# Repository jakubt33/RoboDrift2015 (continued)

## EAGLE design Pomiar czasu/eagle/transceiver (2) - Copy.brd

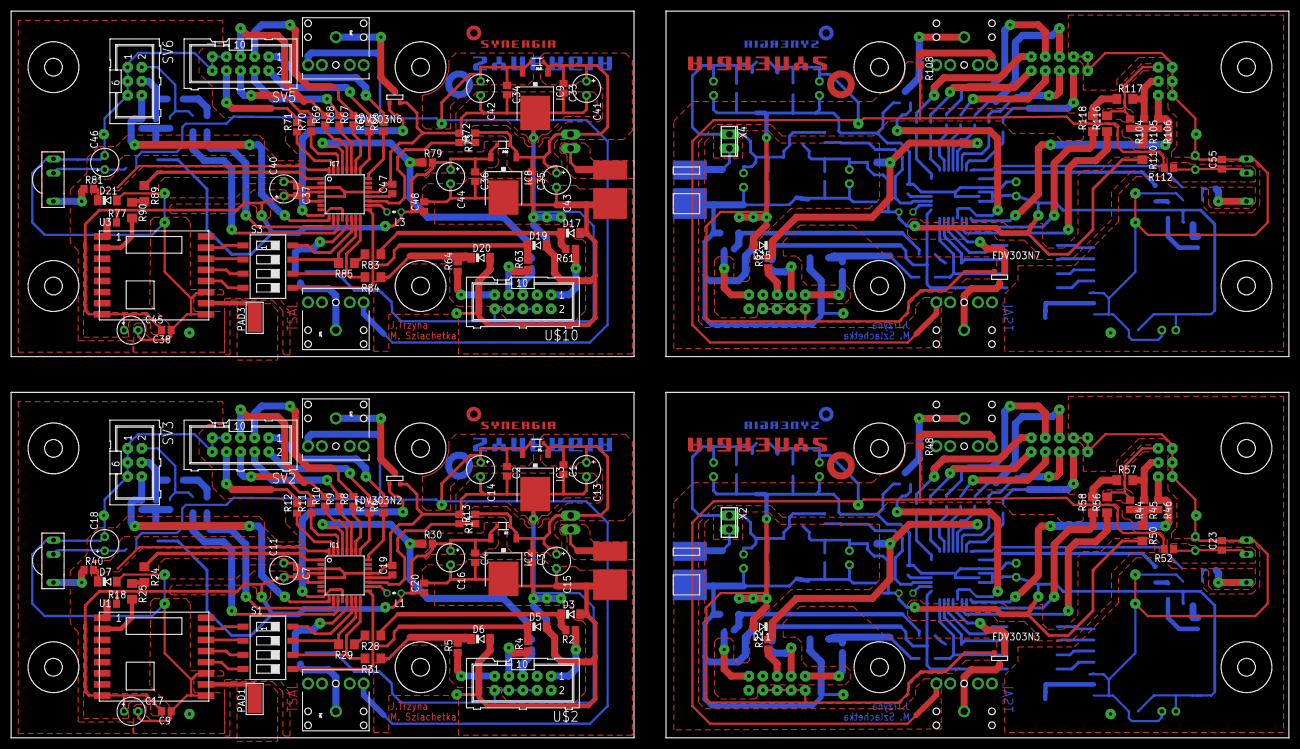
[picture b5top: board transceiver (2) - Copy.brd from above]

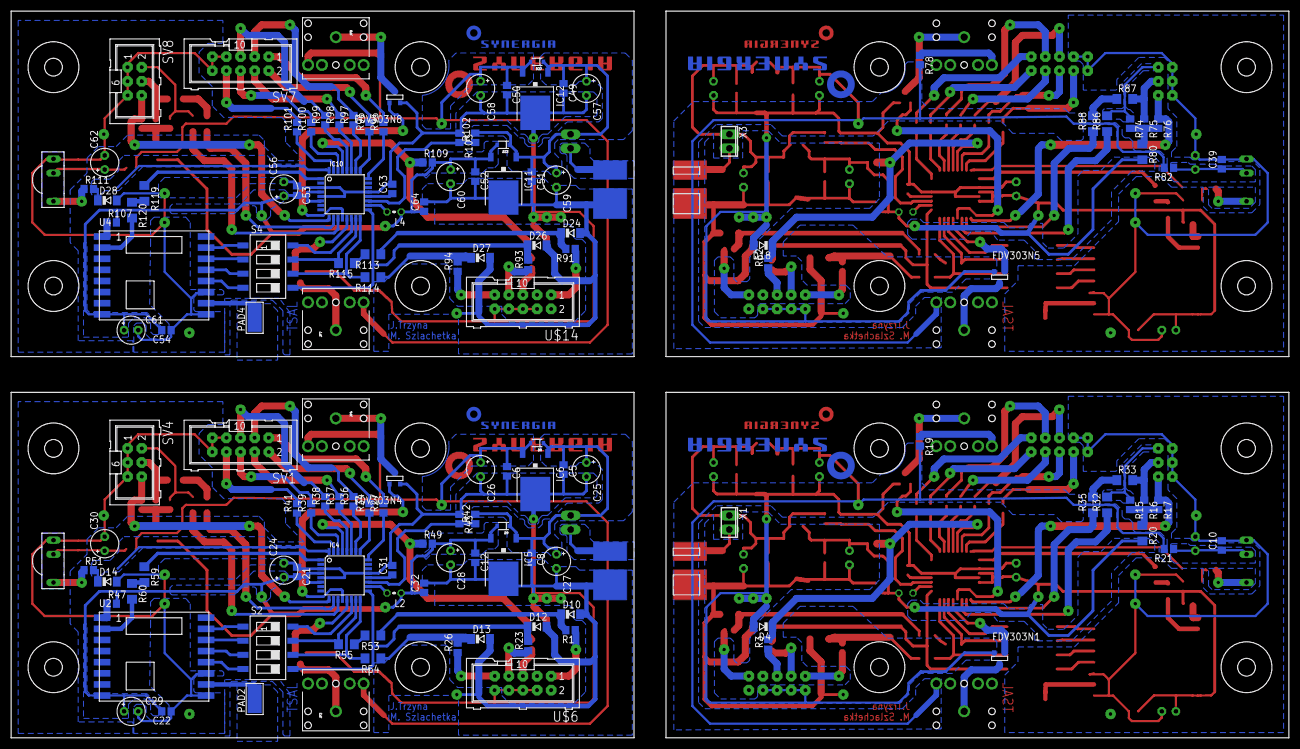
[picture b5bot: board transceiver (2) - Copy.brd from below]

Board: 2 copper layers, 229.9 x 130.7 mm, 288 parts (144 on the bottom side), 232 nets.

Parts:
C1, C2, C3, C4, C5, C6, C7, C8, C9, C10, C12, C19, C20, C21, C22, C23, C31, C32, C33, C34, C35, C36, C37, C38, C39, C47, C48, C49, C50, C51, C52, C53, C54, C55, C63, C64: 100n; C0805
C11, C17, C24, C29, C40, C45, C56, C61: 22u; E2,5-5
C13, C14, C15, C16, C25, C26, C27, C28, C41, C42, C43, C44, C57, C58, C59, C60: 47u; E2,5-5
C18, C30, C46, C62: 4,7u; E2,5-5
D1, D2, D8, D9, D15, D16, D22, D23: BAS16HT1G; SOD-323
D3, D4, D5, D6, D7, D10, D11, D12, D13, D14, D17, D18, D19, D20, D21, D24, D25, D26, D27, D28: SOD80C
FDV303N1, FDV303N2, FDV303N3, FDV303N4, FDV303N5, FDV303N6, FDV303N7, FDV303N8: SOT-23
IC1, IC4, IC7, IC10: MEGA8-AI; TQFP32-08
IC2, IC5, IC8, IC11: LF33; TO252
IC3, IC6, IC9, IC12: LF50; TO252
JP1, JP2, JP3, JP4, JP5, JP6, JP7, JP8: AUDIO-JACK
L1, L2, L3, L4: 0204V
PAD1, PAD2, PAD3, PAD4: WIREPADSMD5-2,5; 5-2,5
R1, R2, R3, R4, R5, R22, R23, R26, R61, R62, R63, R64, R91, R92, R93, R94: 330k; R0805
R6, R7, R8, R9, R10, R12, R27, R34, R36, R37, R38, R41, R65, R66, R67, R68, R69, R71, R95, R96, R97, R98, R99, R101: 1.2k; R0805
R11, R39, R70, R100: 1,2k; R0805
R13, R15, R16, R17, R18, R30, R42, R44, R45, R46, R47, R49, R72, R74, R75, R76, R77, R79, R102, R104, R105, R106, R107, R109: 10k; R0805
R14, R43, R73, R103: 3,6k; R0805
R19, R48, R78, R108: R0805
R20, R24, R25, R28, R29, R31, R32, R33, R35, R50, R53, R54, R55, R56, R57, R58, R59, R60, R80, R83, R84, R85, R86, R87, R88, R89, R90, R110, R113, R114, R115, R116, R117, R118, R119, R120: 0R; R1206
R21, R40, R51, R52, R81, R82, R111, R112: 220R; R0805
S1, S2, S3, S4: SWS004; SMS-004
SV1, SV2, SV5, SV7: ML10
SV3, SV4, SV6, SV8: ML6
TSOP, TSOP1, TSOP2, TSOP3: TSOP1736; TSOP17XX
U1, U2, U3, U4: RFM69HW; RFM69W-XXXS2
U$1, U$5, U$9, U$13: DEANS.MALE; DEANSM
U$2, U$6, U$10, U$14: ML10
U$3, U$7, U$11, U$15: SYNERGIA_16MM
U$4, U$8, U$12, U$16: SYNERGIA_30MM
X1, X2, X3, X4: 2POL254

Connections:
+3V1: C12.1, C21.2, C22.2, C24.+, C28.+, C29.+, C32.1, D9.2, IC4.4, IC4.6, IC5.2, L2.1, R47.2, R49.2, R50.2, U2.8
+3V2: C36.1, C37.2, C38.2, C40.+, C44.+, C45.+, C48.1, D16.2, IC7.4, IC7.6, IC8.2, L3.1, R77.2, R79.2, R80.2, U3.8
+3V3: C4.1, C7.2, C9.2, C11.+, C16.+, C17.+, C20.1, D2.2, IC1.4, IC1.6, IC2.2, L1.1, R18.2, R20.2, R30.2, U1.8
+3V4: C52.1, C53.2, C54.2, C56.+, C60.+, C61.+, C64.1, D23.2, IC10.4, IC10.6, IC11.2, L4.1, R107.2, R109.2, R110.2, U4.8
+5V: C2.1, C14.+, D1.2, IC3.2, JP1.TIP, R19.2, R21.2
+5V1: C6.1, C26.+, D8.2, IC6.2, JP2.TIP, R48.2, R52.2
+5V2: C34.1, C42.+, D15.2, IC9.2, JP5.TIP, R78.2, R82.2
+5V3: C50.1, C58.+, D22.2, IC12.2, JP7.TIP, R108.2, R112.2
ADC: IC1.19, R13.1, R14.2
ADC1: IC4.19, R42.1, R43.2
ADC2: IC7.19, R72.1, R73.2
ADC3: IC10.19, R102.1, R103.2
DIO0: IC1.1, R24.1
DIO1: IC4.1, R59.1
DIO2: IC7.1, R89.1
DIO3: IC10.1, R119.1
GND: C1.2, C2.2, C3.2, C4.2, C7.1, C9.1, C10.2, C11.-, C13.-, C14.-, C15.-, C16.-, C17.-, C18.-, C19.2, C20.2, D3.A, D4.A, D5.A, D6.A, D7.A, FDV303N1.2, FDV303N2.2, IC1.3, IC1.5, IC1.21, IC2.3, IC3.3, R14.1, SV2.7, SV2.9, SV2.10, SV3.1, SV3.3, SV3.5, TSOP.GND, U1.9, U1.11, U$1.P$NEG, U$2.4, U$2.6, U$2.8, U$2.10
GND1: C5.2, C6.2, C8.2, C12.2, C21.1, C22.1, C23.2, C24.-, C25.-, C26.-, C27.-, C28.-, C29.-, C30.-, C31.2, C32.2, D10.A, D11.A, D12.A, D13.A, D14.A, FDV303N3.2, FDV303N4.2, IC4.3, IC4.5, IC4.21, IC5.3, IC6.3, R43.1, SV1.7, SV1.9, SV1.10, SV4.1, SV4.3, SV4.5, TSOP1.GND, U2.9, U2.11, U$5.P$NEG, U$6.4, U$6.6, U$6.8, U$6.10
GND2: C33.2, C34.2, C35.2, C36.2, C37.1, C38.1, C39.2, C40.-, C41.-, C42.-, C43.-, C44.-, C45.-, C46.-, C47.2, C48.2, D17.A, D18.A, D19.A, D20.A, D21.A, FDV303N5.2, FDV303N6.2, IC7.3, IC7.5, IC7.21, IC8.3, IC9.3, R73.1, SV5.7, SV5.9, SV5.10, SV6.1, SV6.3, SV6.5, TSOP2.GND, U3.9, U3.11, U$9.P$NEG, U$10.4, U$10.6, U$10.8, U$10.10
GND3: C49.2, C50.2, C51.2, C52.2, C53.1, C54.1, C55.2, C56.-, C57.-, C58.-, C59.-, C60.-, C61.-, C62.-, C63.2, C64.2, D24.A, D25.A, D26.A, D27.A, D28.A, FDV303N7.2, FDV303N8.2, IC10.3, IC10.5, IC10.21, IC11.3, IC12.3, R103.1, SV7.7, SV7.9, SV7.10, SV8.1, SV8.3, SV8.5, TSOP3.GND, U4.9, U4.11, U$13.P$NEG, U$14.4, U$14.6, U$14.8, U$14.10
LED1: IC1.24, R6.1
LED2: IC1.25, R7.1
LED3: IC1.26, R8.1
LED4: IC1.27, R9.1
LED5: IC1.28, R10.1
LED6: IC4.24, R27.1
LED7: IC4.25, R34.1
LED8: IC4.26, R36.1
LED9: IC4.27, R37.1
LED10: IC4.28, R38.1
LED11: IC7.24, R65.1
LED12: IC7.25, R66.1
LED13: IC7.26, R67.1
LED14: IC7.27, R68.1
LED15: IC7.28, R69.1
LED16: IC10.24, R95.1
LED17: IC10.25, R96.1
LED18: IC10.26, R97.1
LED19: IC10.27, R98.1
LED20: IC10.28, R99.1
LED_BATT_GR: IC1.30, R11.1
LED_BATT_GR1: IC4.30, R39.1
LED_BATT_GR2: IC7.30, R70.1
LED_BATT_GR3: IC10.30, R100.1
LED_BATT_RED: IC1.31, R12.1
LED_BATT_RED1: IC4.31, R41.1
LED_BATT_RED2: IC7.31, R71.1
LED_BATT_RED3: IC10.31, R101.1
LED_STRIPE: FDV303N2.3, IC1.12
LED_STRIPE1: FDV303N4.3, IC4.12
LED_STRIPE2: FDV303N6.3, IC7.12
LED_STRIPE3: FDV303N8.3, IC10.12
MISO: IC1.16, R31.2, S1.6
MISO1: IC4.16, R54.2, S2.6
MISO2: IC7.16, R84.2, S3.6
MISO3: IC10.16, R114.2, S4.6
MOSI: IC1.15, R29.2, S1.7
MOSI1: IC4.15, R55.2, S2.7
MOSI2: IC7.15, R85.2, S3.7
MOSI3: IC10.15, R115.2, S4.7
unnamed: R40.1, TSOP.OUT
unnamed: IC1.18, L1.2
unnamed: R1.1, U$6.1
unnamed: R2.1, U$2.1
unnamed: R3.1, U$2.5
unnamed: R4.1, U$2.7
unnamed: R5.1, U$2.9
unnamed: R22.1, U$6.5
unnamed: R6.2, SV2.1
unnamed: R7.2, SV2.2
unnamed: R8.2, SV2.3
unnamed: R9.2, SV2.4
unnamed: R10.2, SV2.5
unnamed: FDV303N1.1, JP1.SLEEVE
unnamed: FDV303N2.1, JP3.SLEEVE
unnamed: R11.2, SV2.6
unnamed: R12.2, SV2.8
unnamed: U$1.P$POS, X1.2
unnamed: JP3.TIP, R19.1
unnamed: R18.1, U1.1
unnamed: R23.1, U$6.7
unnamed: R15.2, R16.2, R17.2, R20.1
unnamed: R24.2, R25.1
unnamed: C10.1, C18.+, R21.1, TSOP.V+
unnamed: C19.1, IC1.20
unnamed: C1.1, C3.1, C13.+, C15.+, D1.1, D2.1, IC2.1, IC3.1, R13.2, X1.1
unnamed: PAD1.1, U1.10
unnamed: R28.2, R29.1
unnamed: D3.C, R2.2, R28.1
unnamed: D6.C, R5.2, R31.1
unnamed: R15.1, R32.2, SV3.2
unnamed: R16.1, R33.2, SV3.4
unnamed: R33.1, R35.2
unnamed: S1.3, U1.13
unnamed: S1.2, U1.14
unnamed: S1.4, U1.12
unnamed: S1.1, U1.15
unnamed: R26.1, U$6.9
unnamed: R47.1, U2.1
unnamed: C5.1, C8.1, C25.+, C27.+, D8.1, D9.1, IC5.1, IC6.1, R42.2, X2.1
unnamed: IC4.18, L2.2
unnamed: C31.1, IC4.20
unnamed: R25.2, U1.2
unnamed: PAD2.1, U2.10
unnamed: R27.2, SV1.1
unnamed: R34.2, SV1.2
unnamed: R36.2, SV1.3
unnamed: R37.2, SV1.4
unnamed: R38.2, SV1.5
unnamed: R39.2, SV1.6
unnamed: R41.2, SV1.8
unnamed: U$5.P$POS, X2.2
unnamed: FDV303N3.1, JP2.SLEEVE
unnamed: FDV303N4.1, JP4.SLEEVE
unnamed: JP4.TIP, R48.1
unnamed: R51.1, TSOP1.OUT
unnamed: C23.1, C30.+, R52.1, TSOP1.V+
unnamed: R44.2, R45.2, R46.2, R50.1
unnamed: D10.C, R1.2, R53.1
unnamed: D13.C, R26.2, R54.1
unnamed: R53.2, R55.1
unnamed: R44.1, R56.2, SV4.2
unnamed: R45.1, R57.2, SV4.4
unnamed: R57.1, R58.2
unnamed: S2.1, U2.15
unnamed: S2.2, U2.14
unnamed: S2.3, U2.13
unnamed: S2.4, U2.12
unnamed: R59.2, R60.1
unnamed: R60.2, U2.2
unnamed: R61.1, U$10.1
unnamed: R62.1, U$10.5
unnamed: R63.1, U$10.7
unnamed: R64.1, U$10.9
unnamed: R77.1, U3.1
unnamed: C33.1, C35.1, C41.+, C43.+, D15.1, D16.1, IC8.1, IC9.1, R72.2, X3.1
unnamed: IC7.18, L3.2
unnamed: C47.1, IC7.20
unnamed: PAD3.1, U3.10
unnamed: R65.2, SV5.1
unnamed: R66.2, SV5.2
unnamed: R67.2, SV5.3
unnamed: R68.2, SV5.4
unnamed: R69.2, SV5.5
unnamed: R70.2, SV5.6
unnamed: R71.2, SV5.8
unnamed: U$9.P$POS, X3.2
unnamed: FDV303N5.1, JP5.SLEEVE
unnamed: FDV303N6.1, JP6.SLEEVE
unnamed: JP6.TIP, R78.1
unnamed: R81.1, TSOP2.OUT
unnamed: C39.1, C46.+, R82.1, TSOP2.V+
unnamed: R74.2, R75.2, R76.2, R80.1
unnamed: D17.C, R61.2, R83.1
unnamed: D20.C, R64.2, R84.1
unnamed: R83.2, R85.1
unnamed: R74.1, R86.2, SV6.2
unnamed: R75.1, R87.2, SV6.4
unnamed: R87.1, R88.2
unnamed: S3.1, U3.15
unnamed: S3.2, U3.14
unnamed: S3.3, U3.13
unnamed: S3.4, U3.12
unnamed: R89.2, R90.1
unnamed: R90.2, U3.2
unnamed: R91.1, U$14.1
unnamed: R92.1, U$14.5
unnamed: R93.1, U$14.7
unnamed: R94.1, U$14.9
unnamed: R107.1, U4.1
unnamed: C49.1, C51.1, C57.+, C59.+, D22.1, D23.1, IC11.1, IC12.1, R102.2, X4.1
unnamed: IC10.18, L4.2
unnamed: C63.1, IC10.20
unnamed: PAD4.1, U4.10
unnamed: R95.2, SV7.1
unnamed: R96.2, SV7.2
unnamed: R97.2, SV7.3
unnamed: R98.2, SV7.4
unnamed: R99.2, SV7.5
unnamed: R100.2, SV7.6
unnamed: R101.2, SV7.8
unnamed: U$13.P$POS, X4.2
unnamed: FDV303N7.1, JP7.SLEEVE
unnamed: FDV303N8.1, JP8.SLEEVE
unnamed: JP8.TIP, R108.1
unnamed: R111.1, TSOP3.OUT
unnamed: C55.1, C62.+, R112.1, TSOP3.V+
unnamed: R104.2, R105.2, R106.2, R110.1
unnamed: D24.C, R91.2, R113.1
unnamed: D27.C, R94.2, R114.1
unnamed: R113.2, R115.1
unnamed: R104.1, R116.2, SV8.2
unnamed: R105.1, R117.2, SV8.4
unnamed: R117.1, R118.2
unnamed: S4.1, U4.15
unnamed: S4.2, U4.14
unnamed: S4.3, U4.13
unnamed: S4.4, U4.12
unnamed: R119.2, R120.1
unnamed: R120.2, U4.2
RESET: D4.C, IC1.29, R3.2, R30.1
RESET1: D11.C, IC4.29, R22.2, R49.1
RESET2: D18.C, IC7.29, R62.2, R79.1
RESET3: D25.C, IC10.29, R92.2, R109.1
SCK: D5.C, IC1.17, R4.2, S1.5
SCK1: D12.C, IC4.17, R23.2, S2.5
SCK2: D19.C, IC7.17, R63.2, S3.5
SCK3: D26.C, IC10.17, R93.2, S4.5
SS: IC1.14, S1.8
SS1: IC4.14, S2.8
SS2: IC7.14, S3.8
SS3: IC10.14, S4.8
SWITCH_DOWN: IC1.11, R32.1
SWITCH_DOWN1: IC4.11, R56.1
SWITCH_DOWN2: IC7.11, R86.1
SWITCH_DOWN3: IC10.11, R116.1
SWITCH_OK: IC1.10, R35.1
SWITCH_OK1: IC4.10, R58.1
SWITCH_OK2: IC7.10, R88.1
SWITCH_OK3: IC10.10, R118.1
SWITCH_UP: IC1.9, R17.1, SV3.6
SWITCH_UP1: IC4.9, R46.1, SV4.6
SWITCH_UP2: IC7.9, R76.1, SV6.6
SWITCH_UP3: IC10.9, R106.1, SV8.6
TSAL_ENABLE: FDV303N1.3, IC1.13
TSAL_ENABLE1: FDV303N3.3, IC4.13
TSAL_ENABLE2: FDV303N5.3, IC7.13
TSAL_ENABLE3: FDV303N7.3, IC10.13
TSOP_OUT: D7.C, IC1.32, R40.2
TSOP_OUT1: D14.C, IC4.32, R51.2
TSOP_OUT2: D21.C, IC7.32, R81.2
TSOP_OUT3: D28.C, IC10.32, R111.2

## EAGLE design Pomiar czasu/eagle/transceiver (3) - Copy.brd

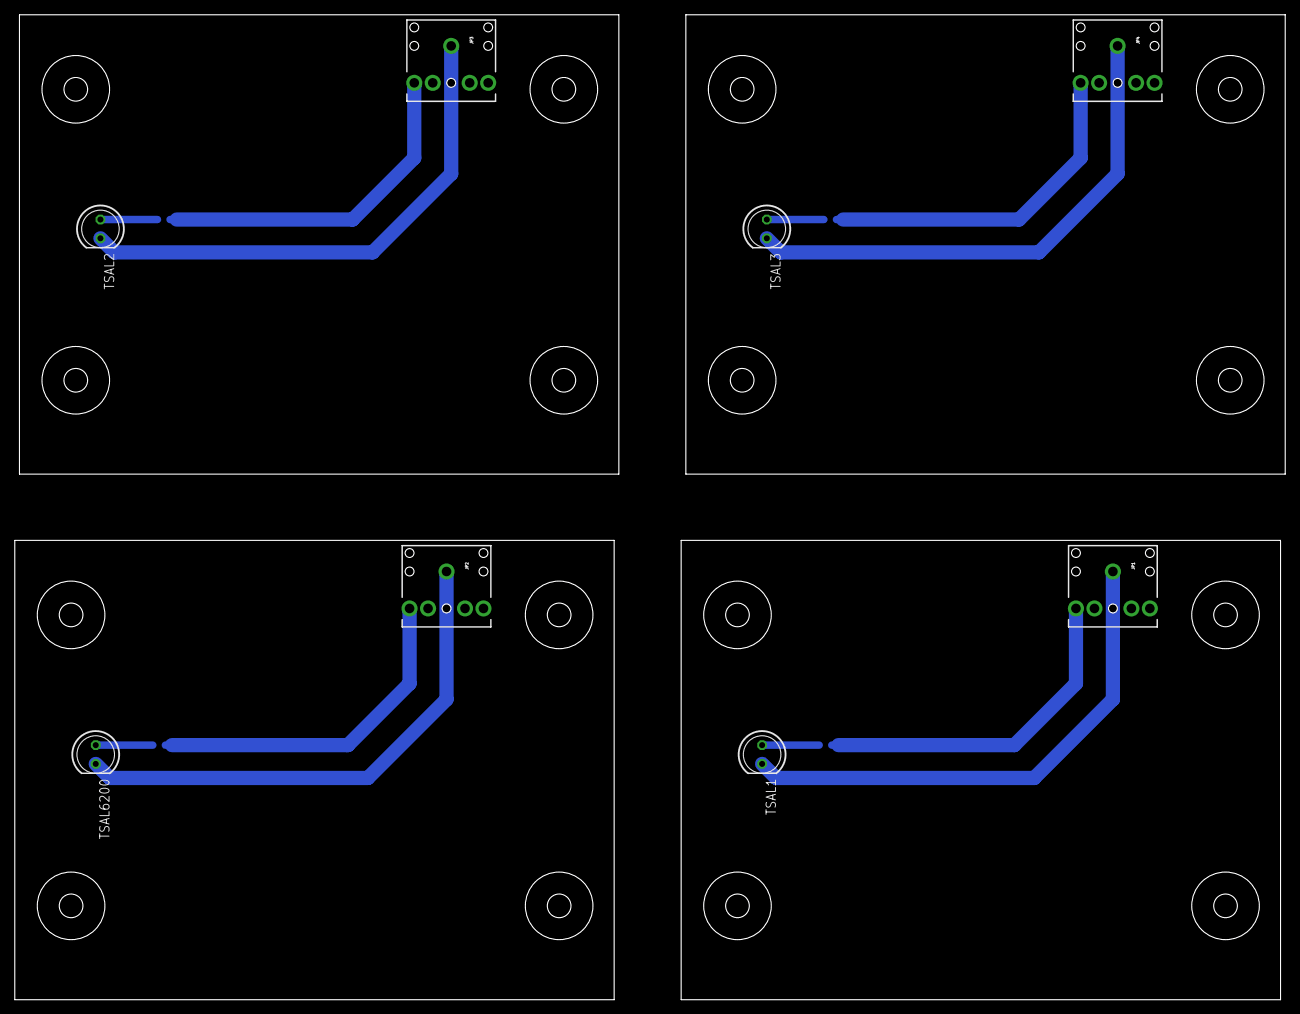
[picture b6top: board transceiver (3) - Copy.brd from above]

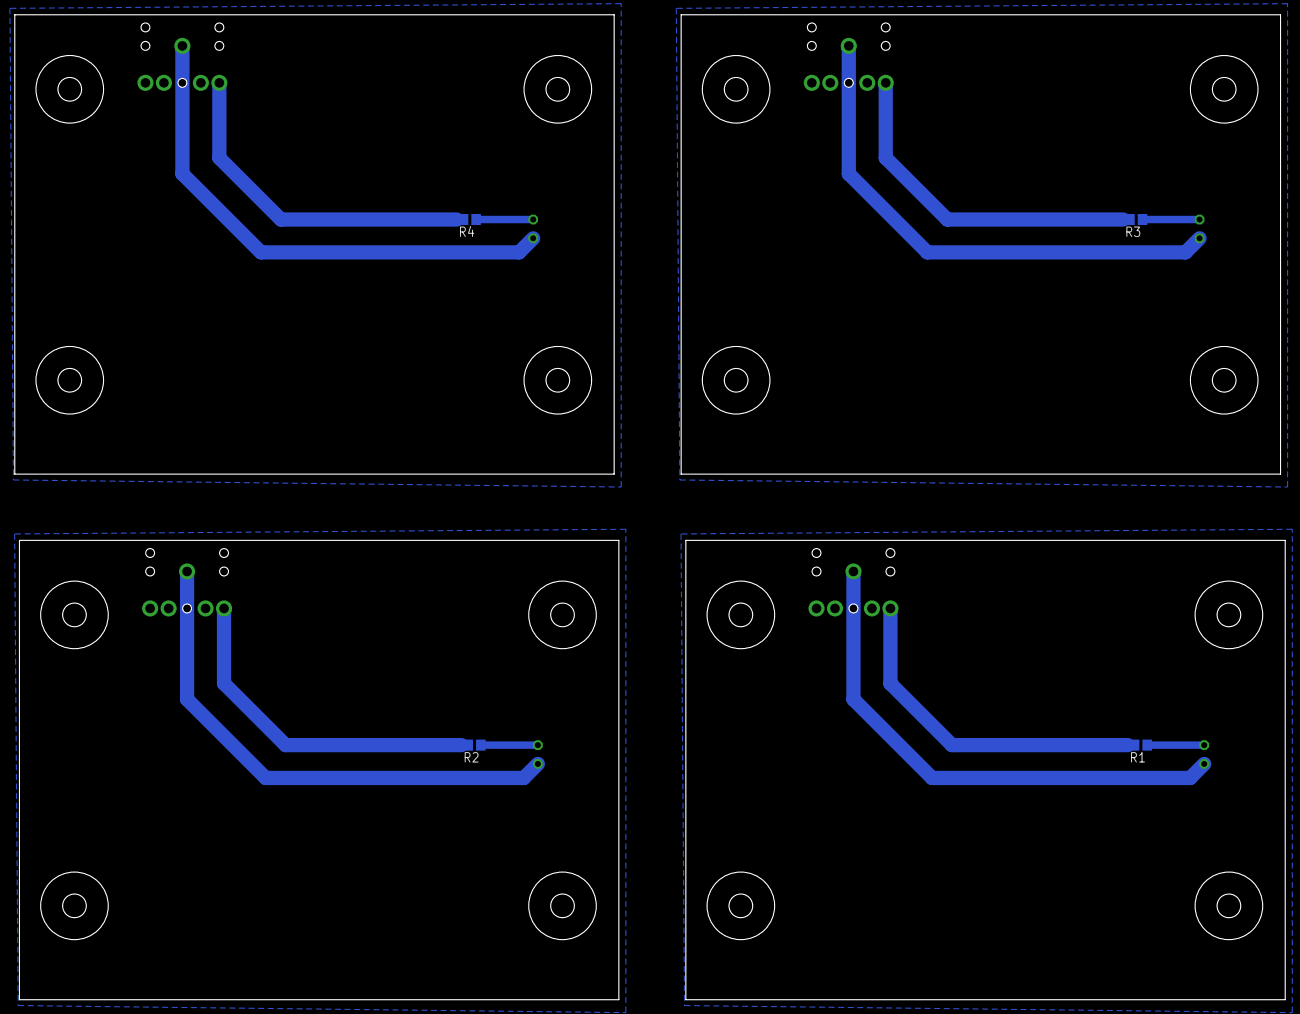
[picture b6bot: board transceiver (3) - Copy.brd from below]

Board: 2 copper layers, 171.9 x 133.3 mm, 12 parts (4 on the bottom side), 12 nets.

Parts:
JP1, JP2, JP3, JP4: AUDIO-JACK
R1, R2, R3, R4: 36,5R; R0805
TSAL1, TSAL2, TSAL3, TSAL6200: LED5MM

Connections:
unnamed: JP1.SLEEVE, TSAL1.K
unnamed: JP1.TIP, R2.2
unnamed: JP2.TIP, R1.2
unnamed: R2.1, TSAL1.A
unnamed: JP3.SLEEVE, TSAL2.K
unnamed: JP3.TIP, R3.2
unnamed: R3.1, TSAL2.A
unnamed: R1.1, TSAL6200.A
unnamed: JP4.SLEEVE, TSAL3.K
unnamed: JP4.TIP, R4.2
unnamed: R4.1, TSAL3.A
unnamed: JP2.SLEEVE, TSAL6200.K

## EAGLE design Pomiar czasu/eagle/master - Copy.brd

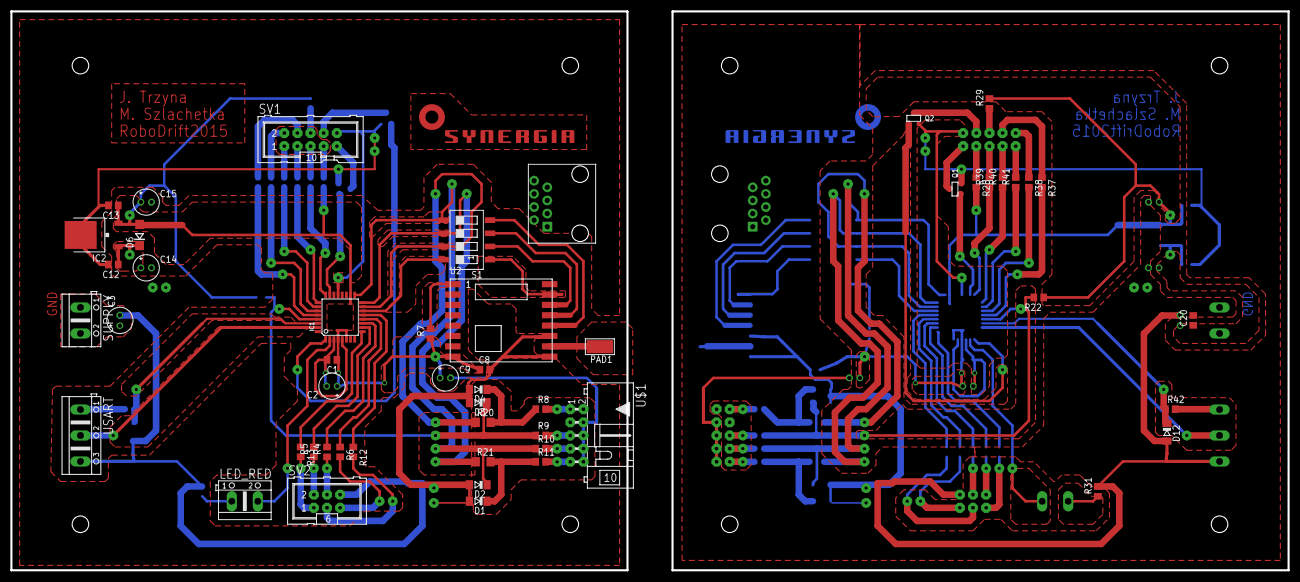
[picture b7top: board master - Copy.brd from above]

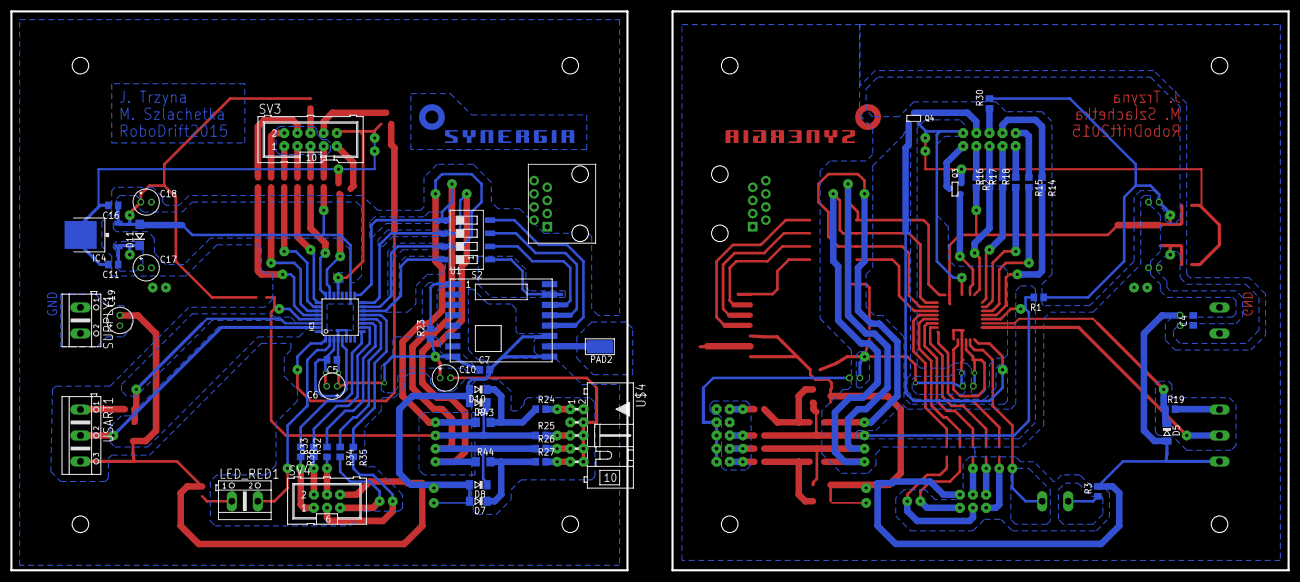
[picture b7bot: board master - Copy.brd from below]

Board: 2 copper layers, 246.7 x 107.9 mm, 106 parts (53 on the bottom side), 102 nets.

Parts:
C1, C4, C5, C7, C8, C11, C12, C13, C16, C20: 100n; C0805
C2, C6: 22uF; E2-5
C3, C19: 220uF; E2-5
C9, C10, C14, C15, C17, C18: 4.7uF; E2-5
D1, D2, D3, D4, D5, D7, D8, D9, D10, D12: 3.3V; SOD80C
D6, D11: BAS16HT1G; DO214AC
IC1, IC3: MEGA8-AI; TQFP32-08
IC2, IC4: lf33; TO252
LED_RED, LED_RED1: AK500/2
PAD1, PAD2: WIREPADSMD5-2,5; 5-2,5
Q1, Q2, Q3, Q4: SOT-23
R1, R7, R22, R23: 10k; R0805
R2, R3, R28, R29, R30, R31: 15R; R0805
R4, R5, R6, R12, R13, R14, R15, R16, R17, R18, R32, R33, R34, R35, R36, R37, R38, R39, R40, R41: 470; R0805
R8, R9, R10, R11, R19, R24, R25, R26, R27, R42: 220; R0805
R20, R21, R43, R44: 0R; R1206
S1, S2: SWS004; SMS-004
SUPPLY, SUPPLY1: AK500/2
SV1, SV3: ML10
SV2, SV4: ML6
U1, U2: RFM69HW; RFM69W-XXXS2
U$1, U$4: AVR_SPI_PROG2PTH2; ML10L
U$2, U$5: RJ45-8PTH; RJ45-8
U$3, U$6: SYNERGIA_30MM
USART, USART1: AK500/3

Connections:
+3V1: C5.1, C6.+, C7.1, C10.+, C16.1, C18.+, D11.A, IC3.4, IC3.6, IC3.18, IC4.2, R22.1, R23.1, R28.2, R29.2, U1.8
+3V3: C1.1, C2.+, C8.1, C9.+, C13.1, C15.+, D6.A, IC1.4, IC1.6, IC1.18, IC2.2, R1.1, R2.2, R7.1, R30.2, U2.8
GND: C1.2, C2.-, C3.-, C4.2, C8.2, C9.-, C12.2, C13.2, C14.-, C15.-, D1.A, D2.A, D3.A, D4.A, D5.A, IC1.3, IC1.5, IC1.21, IC2.3, Q3.2, Q4.2, R3.2, SUPPLY.1, SV1.10, SV2.6, U2.9, U2.11, U$1.4, U$1.6, U$1.8, U$1.10, USART.3
GND1: C5.2, C6.-, C7.2, C10.-, C11.2, C16.2, C17.-, C18.-, C19.-, C20.2, D7.A, D8.A, D9.A, D10.A, D12.A, IC3.3, IC3.5, IC3.21, IC4.3, Q1.2, Q2.2, R31.2, SUPPLY1.1, SV3.10, SV4.6, U1.9, U1.11, U$4.4, U$4.6, U$4.8, U$4.10, USART1.3
LED_FALSTART: R30.1, SV1.6
LED_FALSTART1: R29.1, SV3.6
LED_FALSTART_GATE: IC1.1, Q4.1
LED_FALSTART_GATE1: IC3.1, Q2.1
LED_FALSTART_GND: Q4.3, SV1.8
LED_FALSTART_GND1: Q2.3, SV3.8
LED_GO: R2.1, SV1.7
LED_GO1: R28.1, SV3.7
LED_GO_GATE: IC1.23, Q3.1
LED_GO_GATE1: IC3.23, Q1.1
LED_GO_GND: Q3.3, SV1.9
LED_GO_GND1: Q1.3, SV3.9
LED_RED: IC1.2, LED_RED.2
LED_RED1: IC3.2, LED_RED1.2
LED_S1: IC1.9, R13.1
LED_S2: IC1.10, R5.2
LED_S3: IC1.13, R12.1
LED_S4: IC1.11, R4.2
LED_S5: IC1.12, R6.1
LED_S6: IC3.9, R36.1
LED_S7: IC3.13, R35.1
LED_S8: IC3.12, R34.1
LED_S9: IC3.10, R33.2
LED_S10: IC3.11, R32.2
LED_Y1: IC1.26, R18.1
LED_Y2: IC1.27, R15.2
LED_Y3: IC1.25, R17.1
LED_Y4: IC1.28, R14.2
LED_Y5: IC1.24, R16.1
LED_Y6: IC3.26, R41.1
LED_Y7: IC3.27, R38.2
LED_Y8: IC3.25, R40.1
LED_Y9: IC3.28, R37.2
LED_Y10: IC3.24, R39.1
MISO: IC1.16, R21.1, S1.6
MISO1: IC3.16, R44.1, S2.6
MOSI: IC1.15, R20.1, S1.7
MOSI1: IC3.15, R43.1, S2.7
unnamed: D1.C, R11.1, R21.2
unnamed: D4.C, R8.1, R20.2
unnamed: LED_RED.1, R3.1
unnamed: R4.1, SV2.4
unnamed: R5.1, SV2.2
unnamed: R6.2, SV2.5
unnamed: R7.2, U2.1
unnamed: S1.1, U2.15
unnamed: PAD1.1, U2.10
unnamed: S1.4, U2.12
unnamed: S1.3, U2.13
unnamed: S1.2, U2.14
unnamed: R8.2, U$1.1
unnamed: R11.2, U$1.9
unnamed: R10.2, U$1.7
unnamed: R9.2, U$1.5
unnamed: R12.2, SV2.3
unnamed: R13.2, SV2.1
unnamed: R14.1, SV1.4
unnamed: R15.1, SV1.2
unnamed: R16.2, SV1.5
unnamed: R17.2, SV1.3
unnamed: R18.2, SV1.1
unnamed: R19.2, USART.1
unnamed: R23.2, U1.1
unnamed: PAD2.1, U1.10
unnamed: R24.2, U$4.1
unnamed: R27.2, U$4.9
unnamed: R26.2, U$4.7
unnamed: R25.2, U$4.5
unnamed: LED_RED1.1, R31.1
unnamed: R32.1, SV4.4
unnamed: R33.1, SV4.2
unnamed: R34.2, SV4.5
unnamed: R35.2, SV4.3
unnamed: R36.2, SV4.1
unnamed: R37.1, SV3.4
unnamed: R38.1, SV3.2
unnamed: R39.2, SV3.5
unnamed: R40.2, SV3.3
unnamed: R41.2, SV3.1
unnamed: R42.2, USART1.1
unnamed: D10.C, R24.1, R43.2
unnamed: D7.C, R27.1, R44.2
unnamed: S2.1, U1.15
unnamed: S2.4, U1.12
unnamed: S2.3, U1.13
unnamed: S2.2, U1.14
RESET: D3.C, IC1.29, R1.2, R9.1
RESET1: D9.C, IC3.29, R22.2, R25.1
RX: D5.C, IC1.30, R19.1
RX1: D12.C, IC3.30, R42.1
SCK: D2.C, IC1.17, R10.1, S1.5
SCK1: D8.C, IC3.17, R26.1, S2.5
SS: IC1.14, S1.8
SS1: IC3.14, S2.8
TXD: IC1.31, USART.2
TXD1: IC3.31, USART1.2
VCC: C3.+, C4.1, C12.1, C14.+, D6.C, IC2.1, SUPPLY.2
VCC1: C11.1, C17.+, C19.+, C20.1, D11.C, IC4.1, SUPPLY1.2

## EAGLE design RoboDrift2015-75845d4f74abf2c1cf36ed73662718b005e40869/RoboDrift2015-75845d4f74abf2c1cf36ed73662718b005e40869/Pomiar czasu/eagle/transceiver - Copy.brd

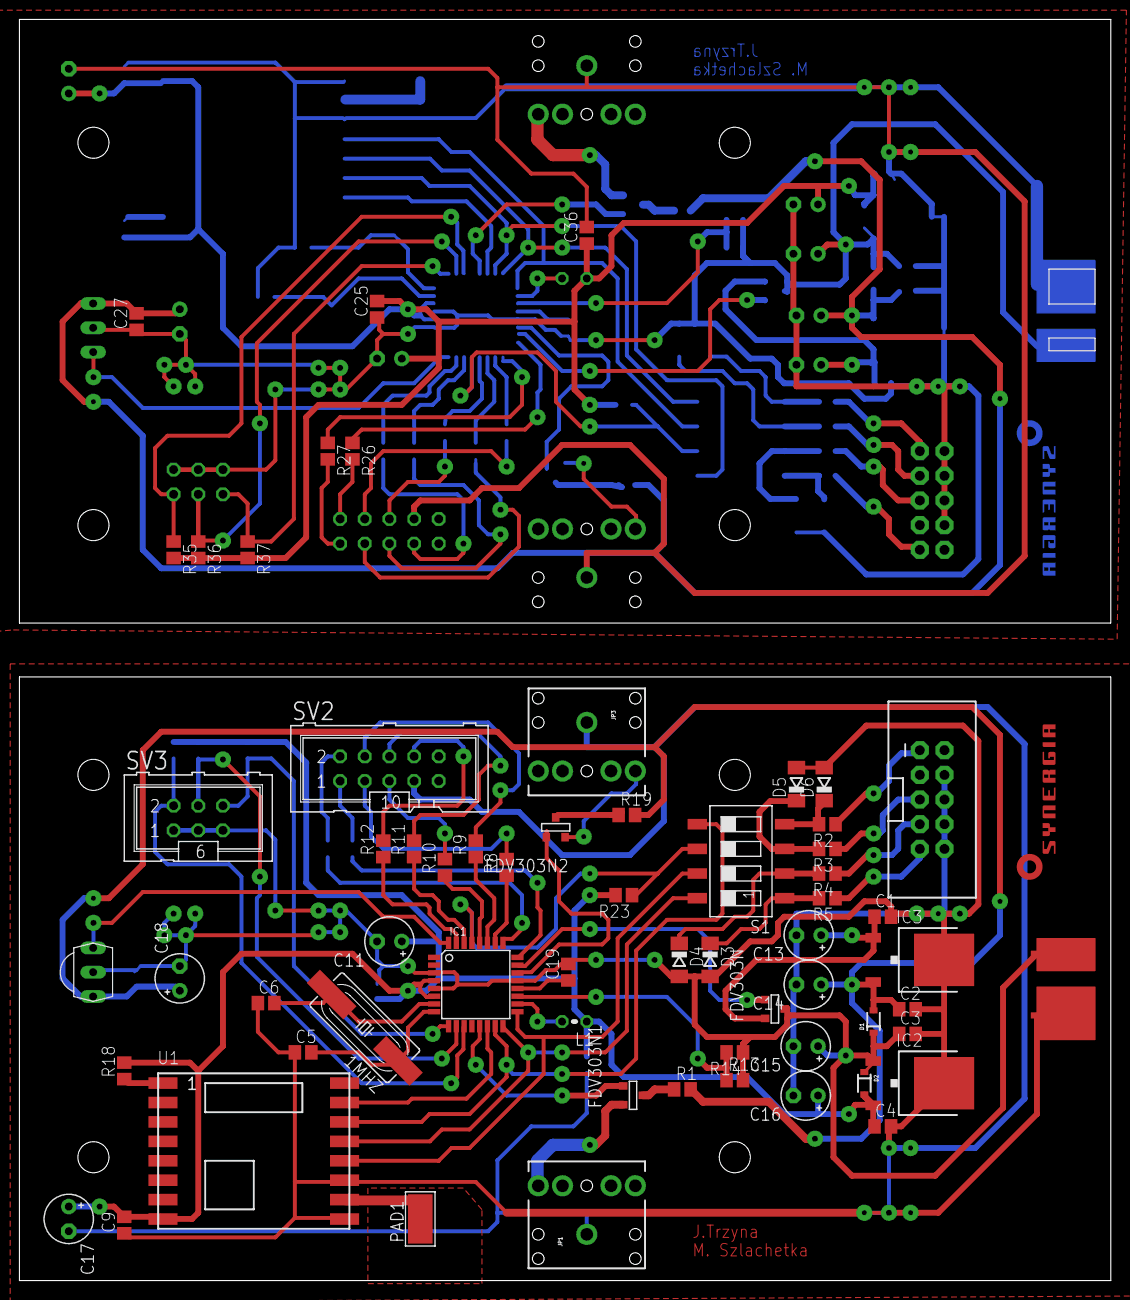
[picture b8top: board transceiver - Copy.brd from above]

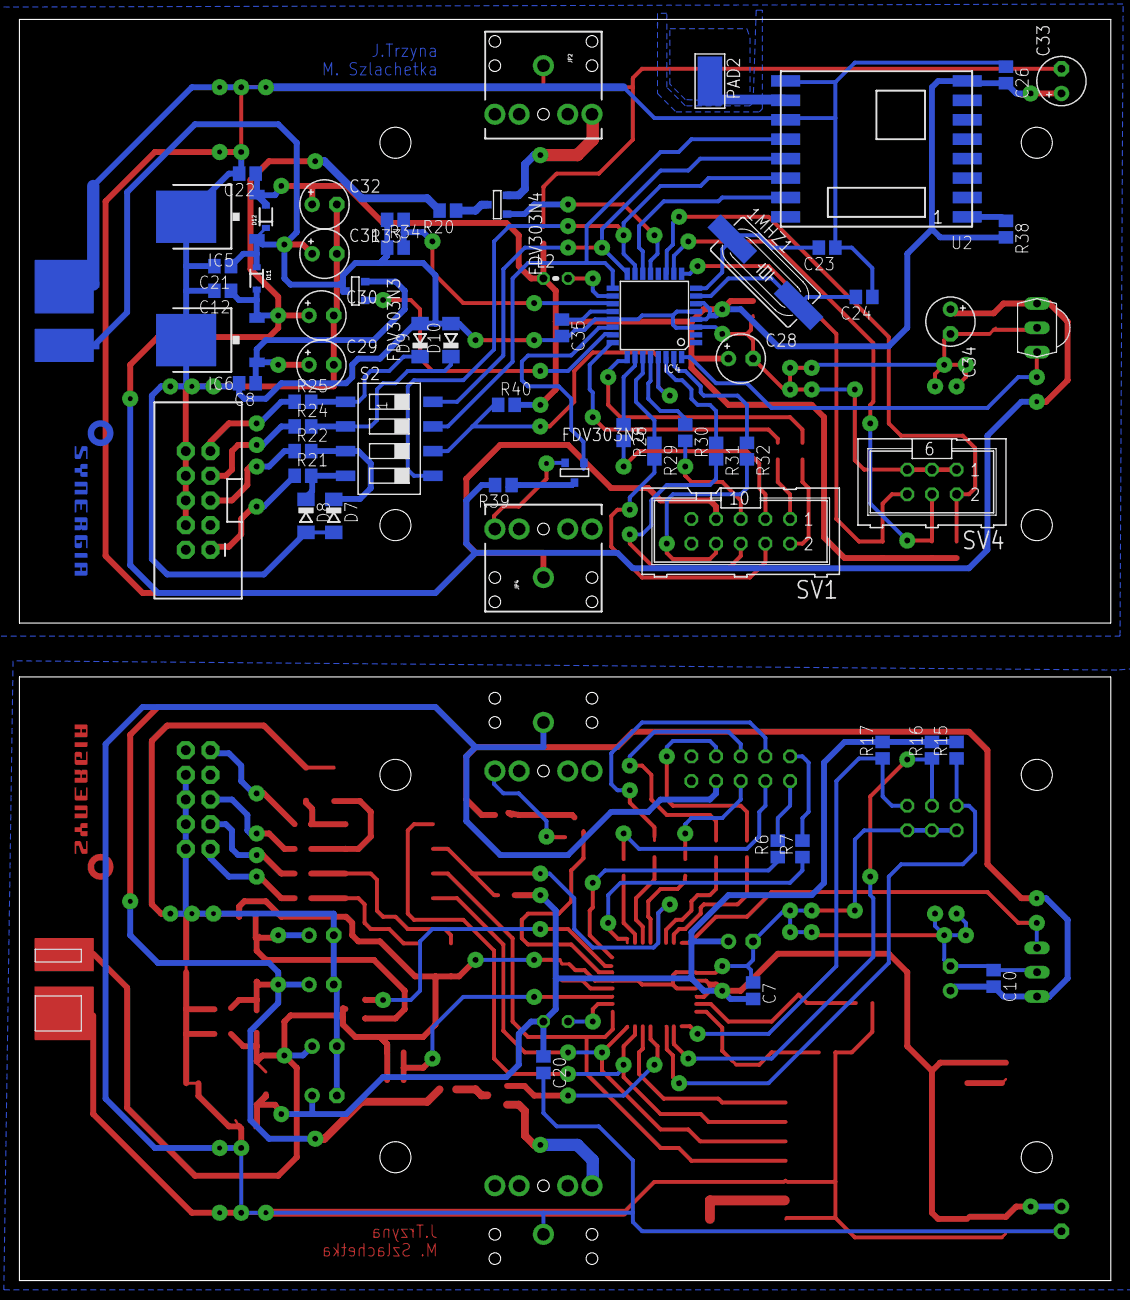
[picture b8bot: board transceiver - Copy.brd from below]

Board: 2 copper layers, 112.4 x 129.9 mm, 126 parts (63 on the bottom side), 100 nets.

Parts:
1MHZ, 1MHZ1: HC49UP
C1, C2, C3, C4, C5, C6, C7, C8, C9, C10, C12, C19, C20, C21, C22, C23, C24, C25, C26, C27, C35, C36: C0805
C11, C13, C14, C15, C16, C17, C18, C28, C29, C30, C31, C32, C33, C34: E2,5-5
D1, D2, D11, D12: BAS16HT1G; SOD-323
D3, D4, D5, D6, D7, D8, D9, D10: SOD80C
FDV303N, FDV303N1, FDV303N2, FDV303N3, FDV303N4, FDV303N5: SOT-23
IC1, IC4: MEGA8-AI; TQFP32-08
IC2, IC5: LF33; TO252
IC3, IC6: LF50; TO252
JP1, JP2, JP3, JP4: AUDIO-JACK
L1, L2: 0204V
PAD1, PAD2: WIREPADSMD5-2,5; 5-2,5
R1, R20: 36,5R; R0805
R2, R3, R4, R5, R6, R7, R8, R9, R10, R11, R12, R19, R21, R22, R24, R25, R26, R27, R28, R29, R30, R31, R32, R39: R0805
R13, R18, R33, R38: 10k; R0805
R14, R34: 3,6k; R0805
R15, R16, R17, R23, R35, R36, R37, R40: 1k; R0805
S1, S2: SWS004; SMS-004
SV1, SV2: ML10
SV3, SV4: ML6
TSOP, TSOP1: TSOP4836; TSOP18XX
U1, U2: RFM69HW; RFM69W-XXXS2
U$1, U$4: DEANS.MALE; DEANSM
U$2, U$5: AVR_SPI_PROG2PTH2; 2X5-SHROUDED
U$3, U$6: SYNERGIA_16MM

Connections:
5V_ENABLE: FDV303N.3, IC1.23
5V_ENABLE1: FDV303N3.3, IC4.23
$1S1: C1.2, C2.2, C3.2, C4.2, C5.1, C6.1, C7.1, C9.1, C10.1, C11.-, C13.-, C14.-, C15.-, C16.-, C17.-, C18.-, C19.2, C20.2, D3.A, D4.A, D5.A, D6.A, IC1.3, IC1.5, IC1.21, IC2.3, IC3.3, JP1.SLEEVE, JP3.SLEEVE, R14.1, SV2.7, SV3.1, SV3.3, SV3.5, TSOP.GND, U1.9, U1.11, U$1.P$NEG, U$2.4, U$2.6, U$2.8, U$2.10
$1S2: C8.2, C12.2, C21.2, C22.2, C23.1, C24.1, C25.1, C26.1, C27.1, C28.-, C29.-, C30.-, C31.-, C32.-, C33.-, C34.-, C35.2, C36.2, D7.A, D8.A, D9.A, D10.A, IC4.3, IC4.5, IC4.21, IC5.3, IC6.3, JP2.SLEEVE, JP4.SLEEVE, R34.1, SV1.7, SV4.1, SV4.3, SV4.5, TSOP1.GND, U2.9, U2.11, U$4.P$NEG, U$5.4, U$5.6, U$5.8, U$5.10
+3V1: C22.1, C25.2, C26.2, C28.+, C32.+, C33.+, C36.1, D12.2, IC4.4, IC4.6, IC5.2, L2.1, R35.2, R36.2, R37.2, R38.2, R40.2, U2.8
+3V3: C4.1, C7.2, C9.2, C11.+, C16.+, C17.+, C20.1, D2.2, IC1.4, IC1.6, IC2.2, L1.1, R15.2, R16.2, R17.2, R18.2, R23.2, U1.8
+5V: C2.1, C10.2, C14.+, C18.+, D1.2, IC3.2, R1.2, R19.2, TSOP.VCC
+5V1: C12.1, C27.2, C30.+, C34.+, D11.2, IC6.2, R20.2, R39.2, TSOP1.VCC
ADC: IC1.19, R13.1, R14.2
ADC1: IC4.19, R33.1, R34.2
LED1: IC1.24, R6.1
LED2: IC1.25, R7.1
LED3: IC1.26, R8.1
LED4: IC1.27, R9.1
LED5: IC1.28, R10.1
LED6: IC4.24, R26.1
LED7: IC4.25, R27.1
LED8: IC4.26, R28.1
LED9: IC4.27, R29.1
LED10: IC4.28, R30.1
LED_BATT_GR: IC1.30, R11.1
LED_BATT_GR1: IC4.30, R31.1
LED_BATT_RED: IC1.31, R12.1
LED_BATT_RED1: IC4.31, R32.1
LED_STRIPE: FDV303N2.3, IC1.22
LED_STRIPE1: FDV303N5.3, IC4.22
MISO: IC1.16, S1.8, U1.13
MISO1: IC4.16, S2.8, U2.13
MOSI: IC1.15, S1.5, U1.14
MOSI1: IC4.15, S2.5, U2.14
unnamed: C1.1, C13.+, FDV303N.2, IC3.1
unnamed: IC1.18, L1.2
unnamed: C8.1, C29.+, FDV303N3.2, IC6.1
unnamed: R2.1, U$2.1
unnamed: R3.1, U$2.5
unnamed: R4.1, U$2.7
unnamed: R5.1, U$2.9
unnamed: FDV303N1.1, R1.1
unnamed: R6.2, SV2.1
unnamed: R7.2, SV2.2
unnamed: R8.2, SV2.3
unnamed: R9.2, SV2.4
unnamed: R10.2, SV2.5
unnamed: 1MHZ.2, C6.2, IC1.7
unnamed: 1MHZ.1, C5.2, IC1.8
unnamed: R11.2, SV2.6
unnamed: R12.2, SV2.8
unnamed: R21.1, U$5.1
unnamed: R22.1, U$5.5
unnamed: R18.1, U1.1
unnamed: R24.1, U$5.7
unnamed: FDV303N1.2, JP1.RING
unnamed: FDV303N2.2, JP3.RING
unnamed: FDV303N2.1, R19.1
unnamed: C19.1, IC1.20
unnamed: C3.1, C15.+, D1.1, D2.1, FDV303N.1, IC2.1, R13.2, U$1.P$POS
unnamed: PAD1.1, U1.10
unnamed: D6.C, R2.2, S1.4
unnamed: D5.C, R3.2, S1.3
unnamed: D4.C, R4.2, S1.2
unnamed: D3.C, R5.2, S1.1
unnamed: R25.1, U$5.9
unnamed: 1MHZ1.2, C24.2, IC4.7
unnamed: 1MHZ1.1, C23.2, IC4.8
unnamed: R38.1, U2.1
unnamed: FDV303N4.2, JP2.RING
unnamed: FDV303N5.2, JP4.RING
unnamed: FDV303N5.1, R39.1
unnamed: FDV303N4.1, R20.1
unnamed: C21.1, C31.+, D11.1, D12.1, FDV303N3.1, IC5.1, R33.2, U$4.P$POS
unnamed: IC4.18, L2.2
unnamed: C35.1, IC4.20
unnamed: PAD2.1, U2.10
unnamed: R26.2, SV1.1
unnamed: R27.2, SV1.2
unnamed: R28.2, SV1.3
unnamed: R29.2, SV1.4
unnamed: R30.2, SV1.5
unnamed: R31.2, SV1.6
unnamed: R32.2, SV1.8
unnamed: D8.C, R21.2, S2.4
unnamed: D7.C, R22.2, S2.3
unnamed: D10.C, R24.2, S2.2
unnamed: D9.C, R25.2, S2.1
RESET: IC1.29, R23.1, S1.6
RESET1: IC4.29, R40.1, S2.6
SCK: IC1.17, S1.7, U1.12
SCK1: IC4.17, S2.7, U2.12
SS: IC1.14, U1.15
SS1: IC4.14, U2.15
SWITCH_DOWN: IC1.11, R15.1, SV3.2
SWITCH_DOWN1: IC4.11, R35.1, SV4.2
SWITCH_OK: IC1.10, R16.1, SV3.4
SWITCH_OK1: IC4.10, R36.1, SV4.4
SWITCH_UP: IC1.9, R17.1, SV3.6
SWITCH_UP1: IC4.9, R37.1, SV4.6
TSAL_ENABLE: FDV303N1.3, IC1.13
TSAL_ENABLE1: FDV303N4.3, IC4.13
TSOP_OUT: IC1.32, TSOP.OUT
TSOP_OUT1: IC4.32, TSOP1.OUT

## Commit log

2014-12-12 :lollipop: Added .gitattributes
2014-12-12 schematic of transceiver and list of elements
2014-12-22 3d model
2015-03-07 defines added, demo program
2015-03-18 ADC slave, master project created
2015-03-20 Slave->ctc, tsal modulation
2015-03-20 TSOP: interrupt vector
2015-03-20 tsop(tim1) and adc (tim2) work simultanously
2015-03-21 adc calibrated
    yellow blinking f=1/10Hz - max battery lvl, gradually to f<1Hz - min
    battery lvl.
    red blinking f<1Hz - critically lvl,
    gradually to steady lightening - batt has to be changed
2015-03-23 master->pc done
2015-04-04 RFM69:communication master->sensor works!
2015-04-05 wireless transmission: CRC checks
2015-04-05 AES encription/decription impleemented!
2015-04-05 fail
2015-04-05 (by hardware)selecting node inside the network to communicate with
2015-04-06 acknowledgement of message reception
    improve robustness!
2015-04-06 robust acknowledgement functionality
2015-04-08 few fixex, sendWithRerty() seems not to freeze after a while
2015-04-18 Channel: 442MHz(!!), ping with acknowledgement
2015-04-18 eko rulezzz, TSAL enable onfly if its nessesary
2015-04-18 few fixes, ping-> double sendWithRetry()
2015-05-01 final v1.0
